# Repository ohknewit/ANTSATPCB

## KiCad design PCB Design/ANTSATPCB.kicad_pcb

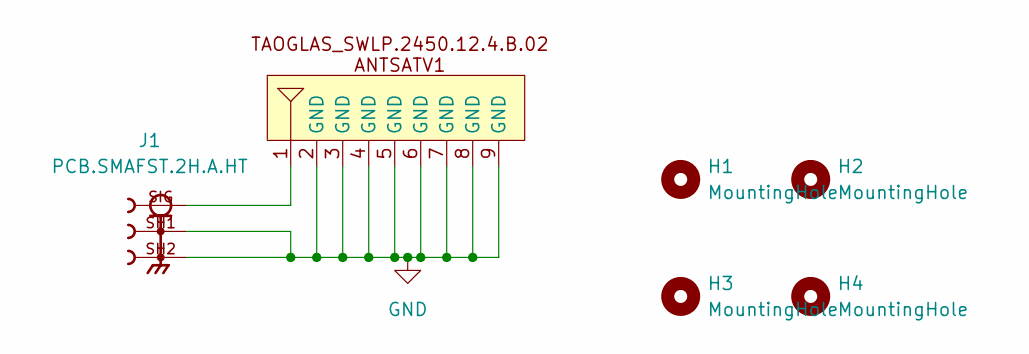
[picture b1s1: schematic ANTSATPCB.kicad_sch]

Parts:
ANT1: ANTSAT1FOOTPRINT
H1, H2, H3, H4: MountingHole; MountingHole_3.2mm_M3_Pad
J1: PCB.SMAFST.2H.A.HT; TAOGLAS_PCB.SMAFST.2H.A.HT; PARTREV SPE-12-8-140/A/WY; DigiKey_Part_Number 931-1178-ND

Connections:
GND: ANT1.2 (GND), ANT1.3 (GND), ANT1.4 (GND), ANT1.5 (GND), ANT1.6 (GND), ANT1.7 (GND), ANT1.8 (GND), ANT1.9 (GND), J1.SH1, J1.SH2
unnamed: ANT1.1, J1.SIG

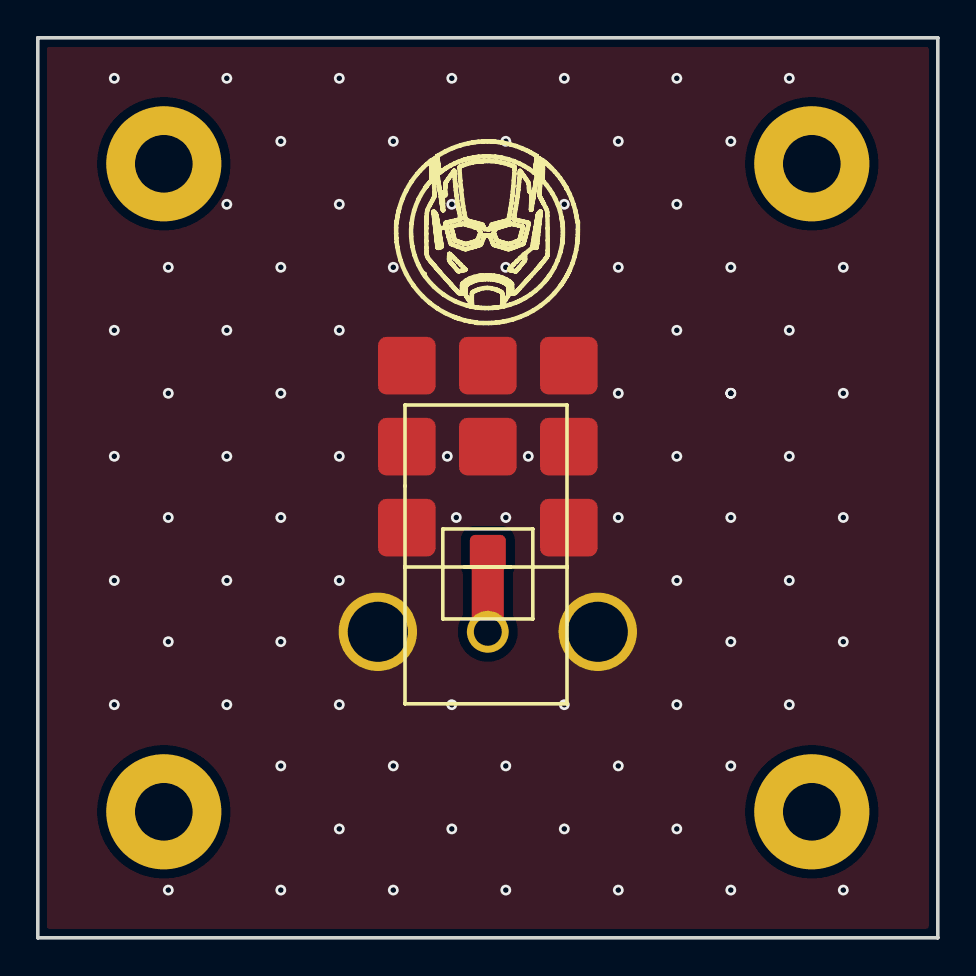
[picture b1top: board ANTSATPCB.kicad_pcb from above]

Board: 2 copper layers, 50.0 x 50.0 mm, 6 parts (1 on the bottom side), 2 nets.

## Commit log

2026-03-30 Create TEST
